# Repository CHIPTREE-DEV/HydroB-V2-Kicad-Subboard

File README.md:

# HydroB-V2-Kicad-Subboard
HydroB-V2-Kicad-Subboard

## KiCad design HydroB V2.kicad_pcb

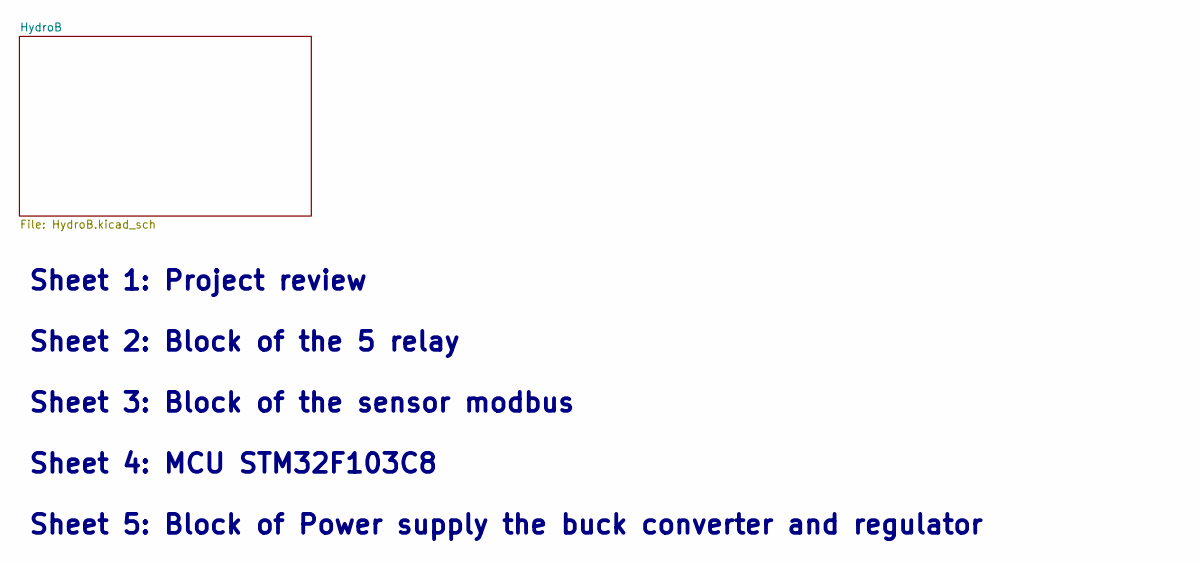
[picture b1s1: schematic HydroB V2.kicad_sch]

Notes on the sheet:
Sheet 1: Project review Sheet 2: Block of the 5 relay Sheet 3: Block of the sensor modbus Sheet 4: MCU STM32F103C8 Sheet 5: Block of Power supply the buck converter and regulator

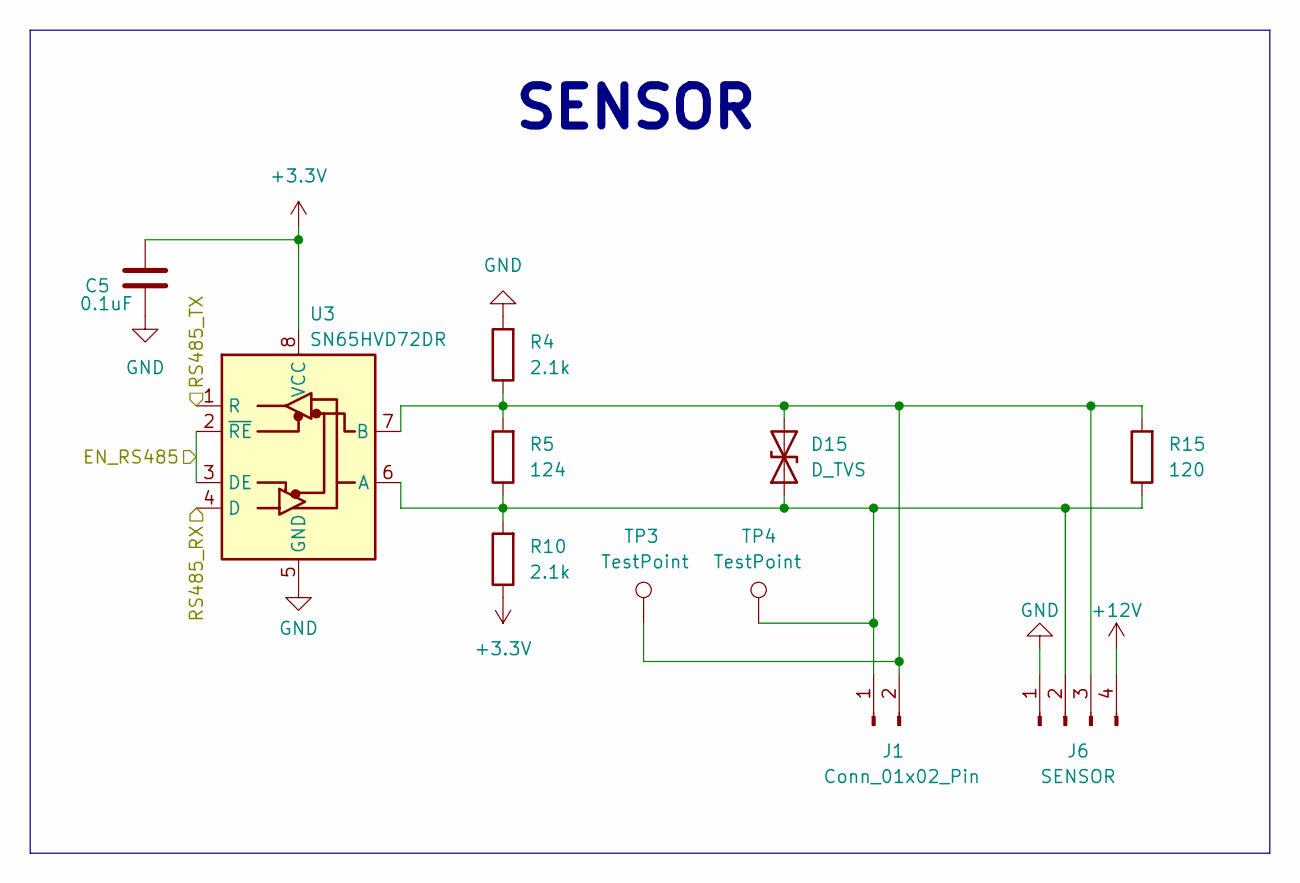
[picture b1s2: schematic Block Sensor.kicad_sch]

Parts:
C5: 0.1uF; C_0603_1608Metric; LCSC C307331
D15: D_TVS; D_SOD-123F
J1: Conn_01x02_Pin; Din sensor
J6: SENSOR; Din sensor 4 Pin
R4, R10: 2.1k; R_0603_1608Metric; LCSC C25744
R5: 124; R_0603_1608Metric; LCSC C25744
R15: 120; R_0603_1608Metric; LCSC C25744
TP3, TP4: TestPoint; TestPoint_Loop_D1.80mm_Drill1.0mm_Beaded
U3: SN65HVD72DR; SOIC-8_3.9x4.9mm_P1.27mm; MFR.Part SN65HVD72DR; LCSC C48125

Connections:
+3.3V: C5.1, R10.1, U3.8 (VCC); also elsewhere on the board
+12V: J6.4; also elsewhere on the board
/HydroB/Block Sensor1/EN_RS485: U3.2 (~RE), U3.3 (DE); also elsewhere on the board
/HydroB/Block Sensor1/RS485_RX: U3.4 (D); also elsewhere on the board
/HydroB/Block Sensor1/RS485_TX: U3.1 (R); also elsewhere on the board
GND: C5.2, J6.1, R4.2, U3.5 (GND); also elsewhere on the board
unnamed: D15.1 (A1), J1.1, J6.2, R5.1, R10.2, R15.1, TP4.1, U3.6 (A)
unnamed: D15.2 (A2), J1.2, J6.3, R4.1, R5.2, R15.2, TP3.1, U3.7 (B)

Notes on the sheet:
SENSOR

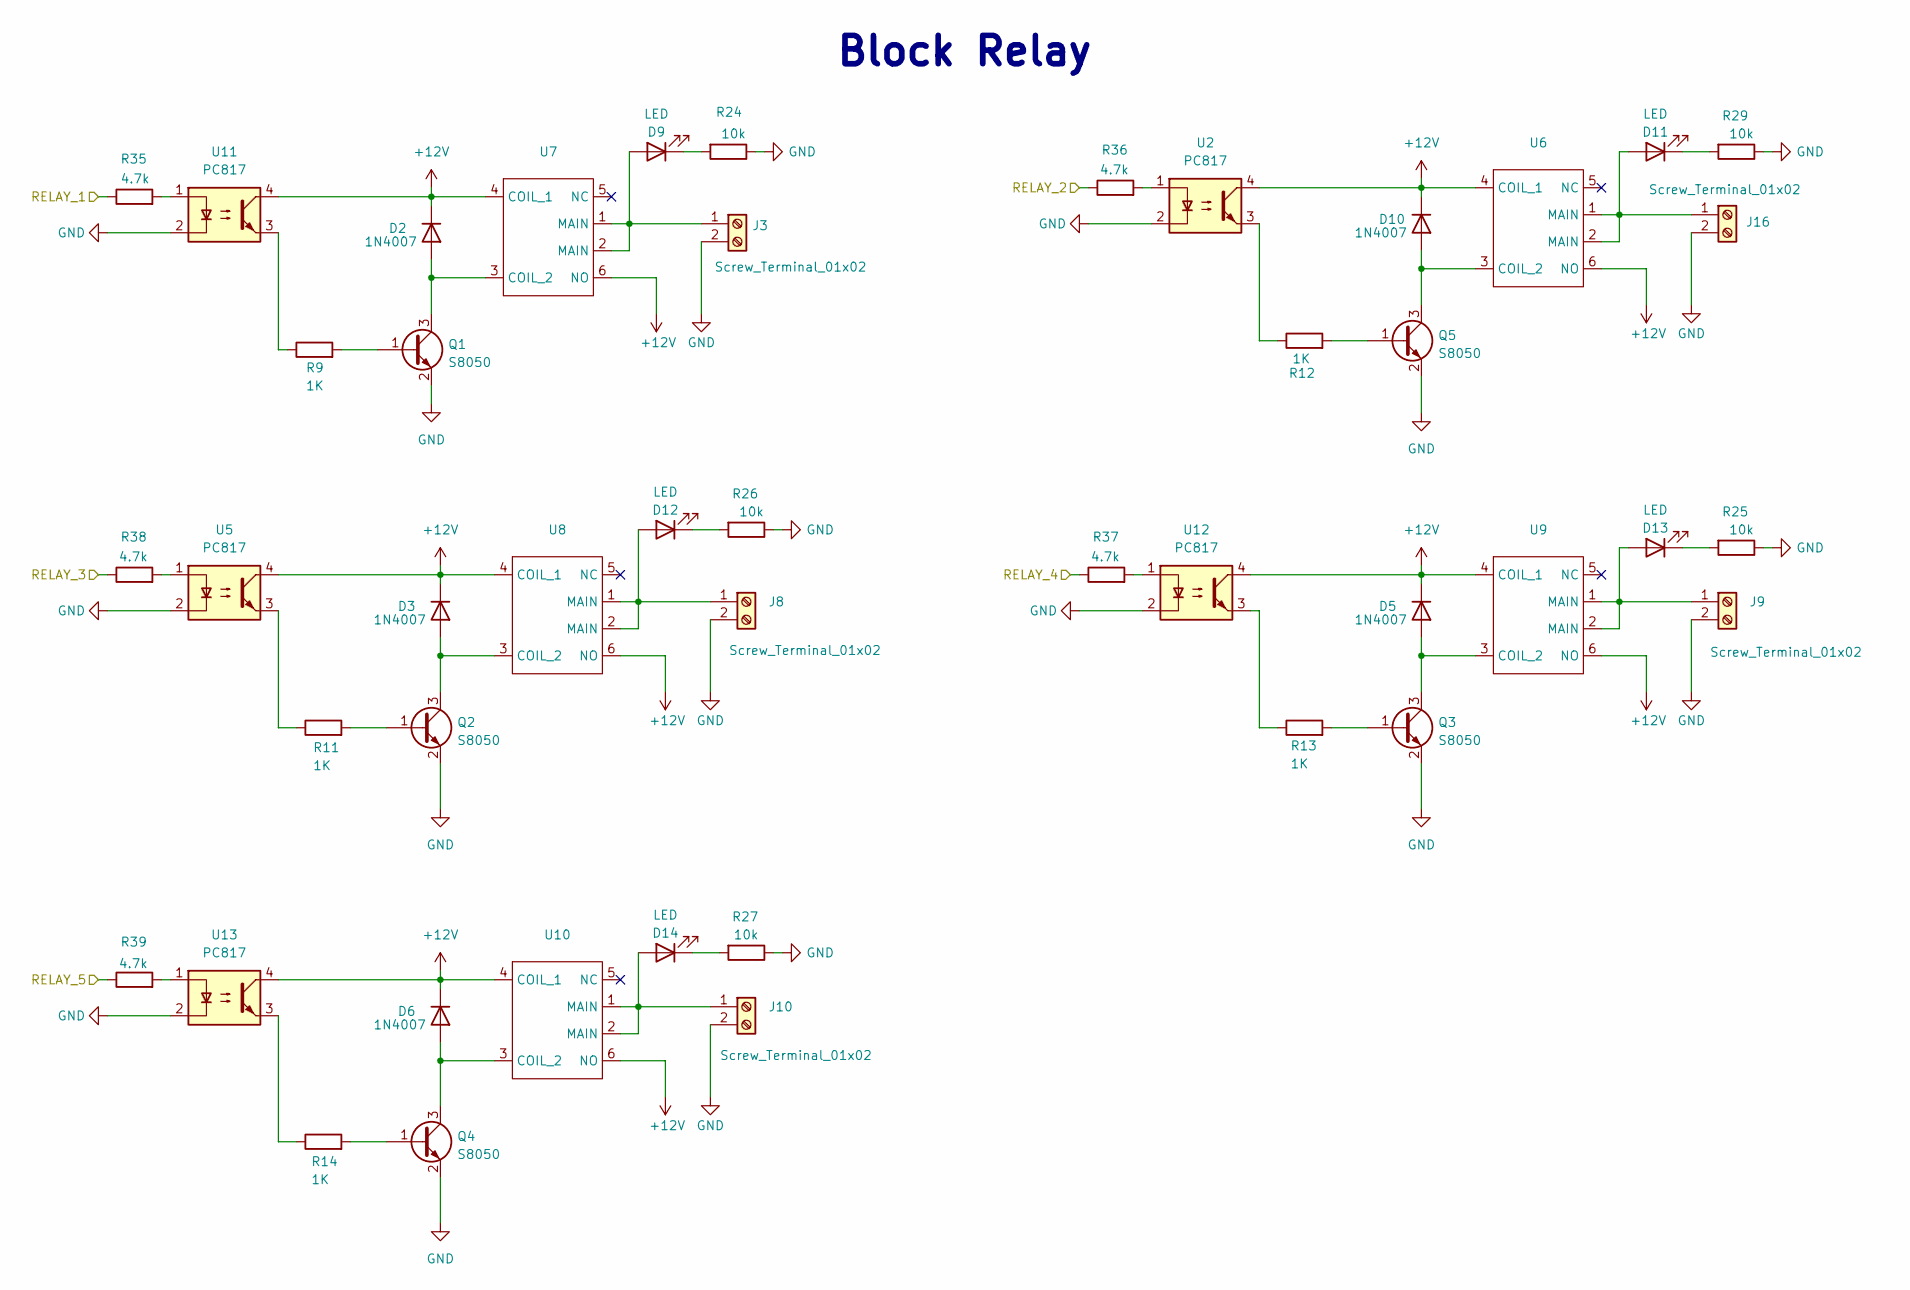
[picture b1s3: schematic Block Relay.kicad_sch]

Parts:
D2, D3, D5, D6, D10: 1N4007; D_SMA
D9, D11, D12, D13, D14: LED; LED_0603_1608Metric
J3, J8, J9, J10, J16: Screw_Terminal_01x02; JST_EH_B2B-EH-A_1x02_P2.50mm_Vertical
Q1, Q2, Q3, Q4, Q5: S8050; SOT-23
R9, R11, R12, R13, R14: 1K; R_0603_1608Metric
R24, R25, R26, R27, R29: 10k; R_0603_1608Metric
R35, R36, R37, R38, R39: 4.7k; R_0603_1608Metric
U2, U5, U11, U12, U13: PC817; DIP-4_W7.62mm_SMDSocket_SmallPads
U6, U7, U8, U9, U10: RELAY-TH_SRS-12VDC-SL

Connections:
+12V: D2.1 (K), D3.1 (K), D5.1 (K), D6.1 (K), D10.1 (K), U2.4, U5.4, U6.4 (COIL_1), U6.6 (NO), U7.4 (COIL_1), U7.6 (NO), U8.4 (COIL_1), U8.6 (NO), U9.4 (COIL_1), U9.6 (NO), U10.4 (COIL_1), U10.6 (NO), U11.4, U12.4, U13.4; also elsewhere on the board
/HydroB/Block Relay1/RELAY_1: R35.1; also elsewhere on the board
/HydroB/Block Relay1/RELAY_2: R36.1; also elsewhere on the board
/HydroB/Block Relay1/RELAY_3: R38.1; also elsewhere on the board
/HydroB/Block Relay1/RELAY_4: R37.1; also elsewhere on the board
/HydroB/Block Relay1/RELAY_5: R39.1; also elsewhere on the board
GND: J3.2, J8.2, J9.2, J10.2, J16.2, Q1.2 (E), Q2.2 (E), Q3.2 (E), Q4.2 (E), Q5.2 (E), R24.1, R25.1, R26.1, R27.1, R29.1, U2.2, U5.2, U11.2, U12.2, U13.2; also elsewhere on the board
unnamed: D2.2 (A), Q1.3 (C), U7.3 (COIL_2)
unnamed: D3.2 (A), Q2.3 (C), U8.3 (COIL_2)
unnamed: D5.2 (A), Q3.3 (C), U9.3 (COIL_2)
unnamed: D6.2 (A), Q4.3 (C), U10.3 (COIL_2)
unnamed: D9.2 (A), J3.1, U7.1 (MAIN), U7.2 (MAIN)
unnamed: D9.1 (K), R24.2
unnamed: D10.2 (A), Q5.3 (C), U6.3 (COIL_2)
unnamed: D11.2 (A), J16.1, U6.1 (MAIN), U6.2 (MAIN)
unnamed: D11.1 (K), R29.2
unnamed: D12.2 (A), J8.1, U8.1 (MAIN), U8.2 (MAIN)
unnamed: D12.1 (K), R26.2
unnamed: D13.2 (A), J9.1, U9.1 (MAIN), U9.2 (MAIN)
unnamed: D13.1 (K), R25.2
unnamed: D14.2 (A), J10.1, U10.1 (MAIN), U10.2 (MAIN)
unnamed: D14.1 (K), R27.2
unnamed: Q1.1 (B), R9.2
unnamed: Q2.1 (B), R11.2
unnamed: Q3.1 (B), R13.2
unnamed: Q4.1 (B), R14.2
unnamed: Q5.1 (B), R12.2
unnamed: R9.1, U11.3
unnamed: R11.1, U5.3
unnamed: R12.1, U2.3
unnamed: R13.1, U12.3
unnamed: R14.1, U13.3
unnamed: R35.2, U11.1
unnamed: R36.2, U2.1
unnamed: R37.2, U12.1
unnamed: R38.2, U5.1
unnamed: R39.2, U13.1

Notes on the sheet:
Block Relay

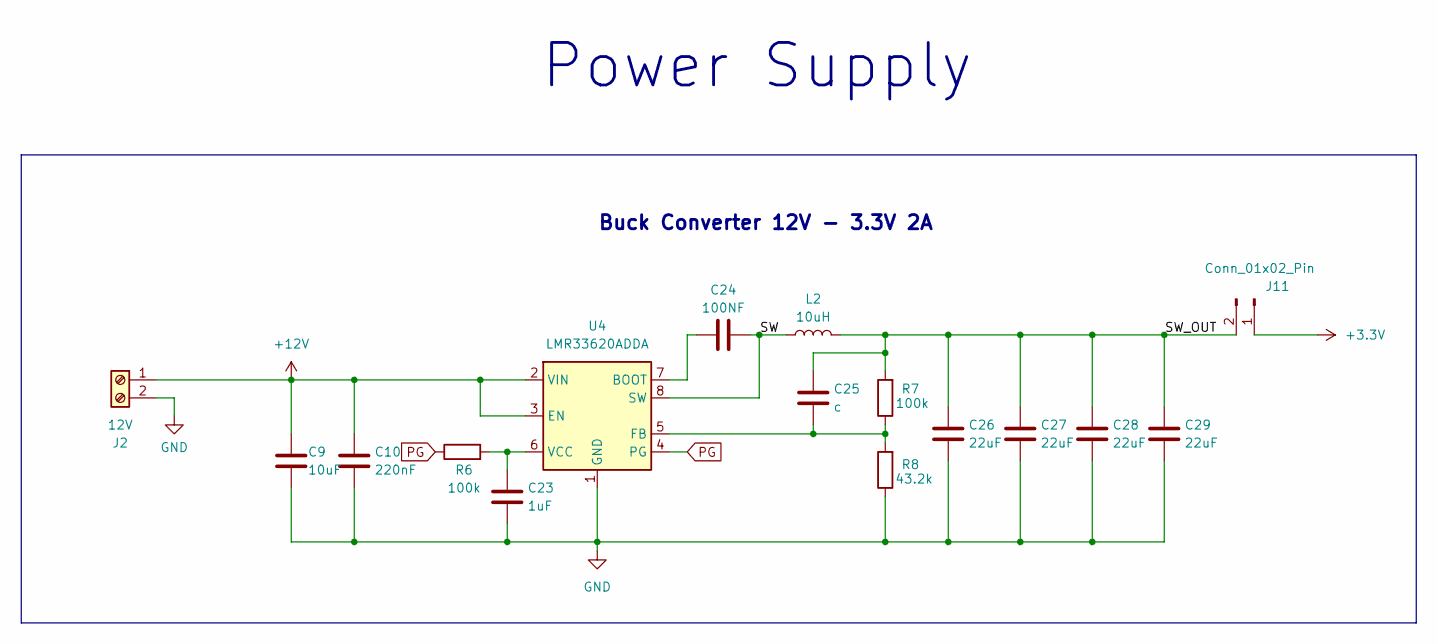
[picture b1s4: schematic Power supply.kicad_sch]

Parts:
C9: 10uF; CP_Elec_4x3
C10: 220nF; C_0805_2012Metric
C23: 1uF; C_0805_2012Metric
C24: 100NF; C_0603_1608Metric
C25: c; C_0805_2012Metric
C26, C27, C28, C29: 22uF; C_0805_2012Metric
J2: 12V; DC conn
J11: Conn_01x02_Pin; PinHeader_1x02_P2.00mm_Vertical
L2: 10uH; L_Bourns_SRP5030T
R6, R7: 100k; R_0603_1608Metric
R8: 43.2k; R_0603_1608Metric
U4: LMR33620ADDA; Texas_HSOP-8-1EP_3.9x4.9mm_P1.27mm_ThermalVias

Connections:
+3.3V: J11.1; also elsewhere on the board
+12V: C9.1, C10.1, J2.1, U4.2 (VIN), U4.3 (EN); also elsewhere on the board
/HydroB/Power Supply1/SW: C24.2, L2.1, U4.8 (SW)
/HydroB/Power Supply1/SW_OUT: C25.1, C26.1, C27.1, C28.1, C29.1, J11.2, L2.2, R7.2
GND: C9.2, C10.2, C23.2, C26.2, C27.2, C28.2, C29.2, J2.2, R8.1, U4.1 (GND), U4.9 (GND); also elsewhere on the board
unnamed: C24.1, U4.7 (BOOT)
unnamed: C25.2, R7.1, R8.2, U4.5 (FB)
unnamed: C23.1, R6.2, U4.6 (VCC)
PG: R6.1, U4.4 (PG)

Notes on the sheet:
Buck Converter 12V - 3.3V 2A
Power Supply

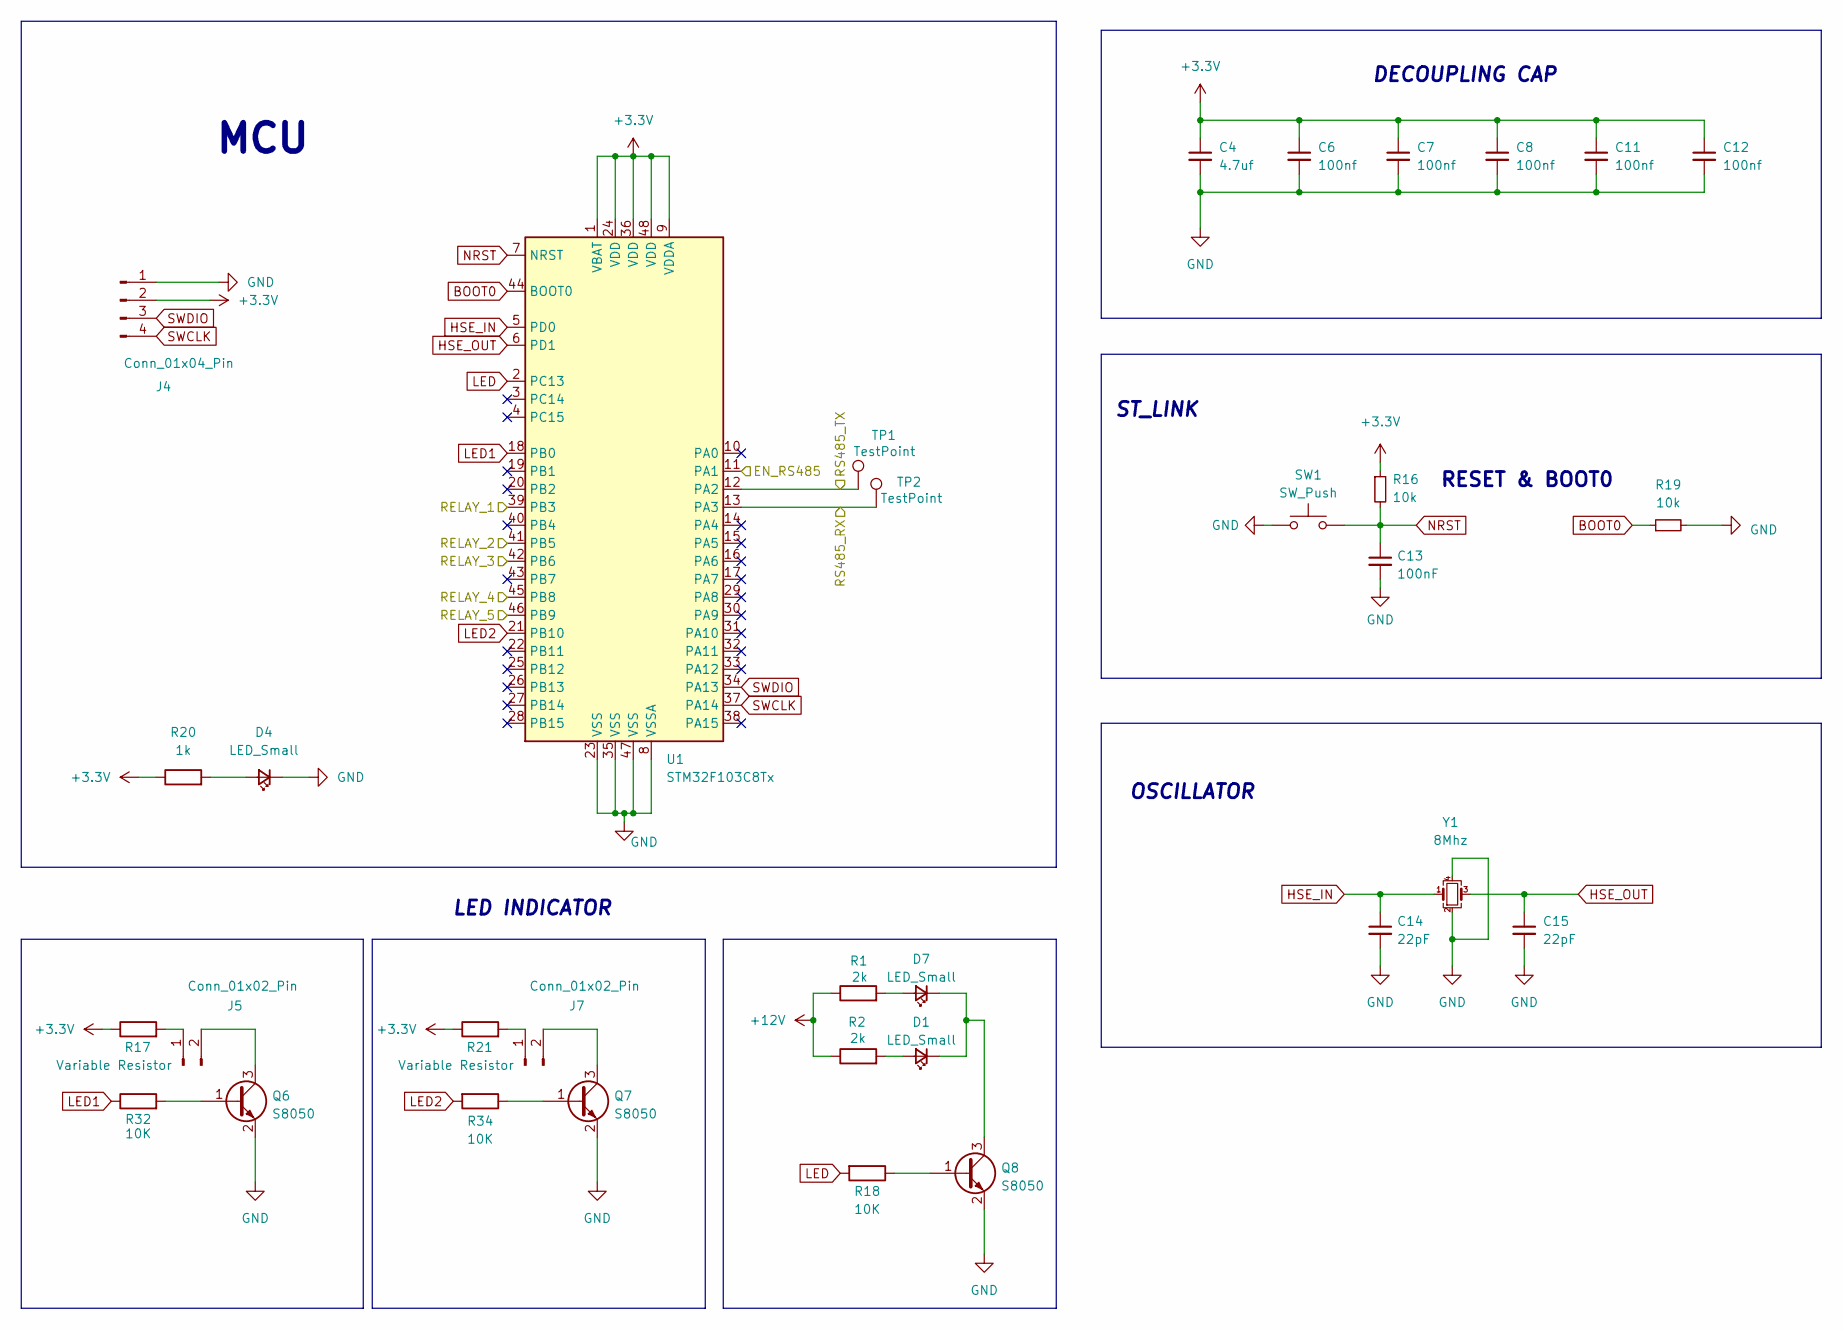
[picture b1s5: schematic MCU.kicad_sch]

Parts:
C4: 4.7uf; C_0805_2012Metric
C6, C7, C8, C11, C12: 100nf; C_0603_1608Metric
C13: 100nF; C_0603_1608Metric
C14, C15: 22pF; C_0603_1608Metric
D1, D4, D7: LED_Small; LED_0805_2012Metric
J4: Conn_01x04_Pin; PinHeader_1x04_P2.00mm_Vertical
J5, J7: Conn_01x02_Pin; JST_EH_B2B-EH-A_1x02_P2.50mm_Vertical
Q6, Q7, Q8: S8050; SOT-23
R1, R2: 2k; R_0603_1608Metric
R16, R19: 10k; R_0603_1608Metric
R17, R21: Variable Resistor; R_0603_1608Metric
R18, R32, R34: 10K; R_0603_1608Metric
R20: 1k; R_0603_1608Metric
SW1: SW_Push; SW_Tactile_SPST_Angled_PTS645Vx39-2LFS
TP1, TP2: TestPoint; TestPoint_Loop_D1.80mm_Drill1.0mm_Beaded
U1: STM32F103C8Tx; LQFP-48_7x7mm_P0.5mm
Y1: 8Mhz; Crystal_SMD_3225-4Pin_3.2x2.5mm

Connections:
+3.3V: C4.1, C6.1, C7.1, C8.1, C11.1, C12.1, J4.2, R16.1, R17.1, R20.1, R21.1, U1.1 (VBAT), U1.9 (VDDA), U1.24 (VDD), U1.36 (VDD), U1.48 (VDD); also elsewhere on the board
+12V: R1.1, R2.1; also elsewhere on the board
/HydroB/Block Relay1/RELAY_1: U1.39 (PB3); also elsewhere on the board
/HydroB/Block Relay1/RELAY_2: U1.41 (PB5); also elsewhere on the board
/HydroB/Block Relay1/RELAY_3: U1.42 (PB6); also elsewhere on the board
/HydroB/Block Relay1/RELAY_4: U1.45 (PB8); also elsewhere on the board
/HydroB/Block Relay1/RELAY_5: U1.46 (PB9); also elsewhere on the board
/HydroB/Block Sensor1/EN_RS485: U1.11 (PA1); also elsewhere on the board
/HydroB/Block Sensor1/RS485_RX: TP1.1, U1.12 (PA2); also elsewhere on the board
/HydroB/Block Sensor1/RS485_TX: TP2.1, U1.13 (PA3); also elsewhere on the board
BOOT0: R19.1, U1.44 (BOOT0)
GND: C4.2, C6.2, C7.2, C8.2, C11.2, C12.2, C13.2, C14.2, C15.2, D4.1 (K), J4.1, Q6.2 (E), Q7.2 (E), Q8.2 (E), R19.2, SW1.1, U1.8 (VSSA), U1.23 (VSS), U1.35 (VSS), U1.47 (VSS), Y1.2, Y1.4; also elsewhere on the board
HSE_IN: C14.1, U1.5 (PD0), Y1.1
HSE_OUT: C15.1, U1.6 (PD1), Y1.3
LED: R18.2, U1.2 (PC13)
LED1: R32.1, U1.18 (PB0)
LED2: R34.2, U1.21 (PB10)
NRST: C13.1, R16.2, SW1.2, U1.7 (NRST)
unnamed: D1.2 (A), R2.2
unnamed: D1.1 (K), D7.1 (K), Q8.3 (C)
unnamed: D4.2 (A), R20.2
unnamed: D7.2 (A), R1.2
unnamed: J5.1, R17.2
unnamed: J5.2, Q6.3 (C)
unnamed: J7.1, R21.2
unnamed: J7.2, Q7.3 (C)
unnamed: Q6.1 (B), R32.2
unnamed: Q7.1 (B), R34.1
unnamed: Q8.1 (B), R18.1
SWCLK: J4.4, U1.37 (PA14)
SWDIO: J4.3, U1.34 (PA13)

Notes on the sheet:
OSCILLATOR
LED INDICATOR
DECOUPLING CAP
ST_LINK
RESET & BOOT0
MCU

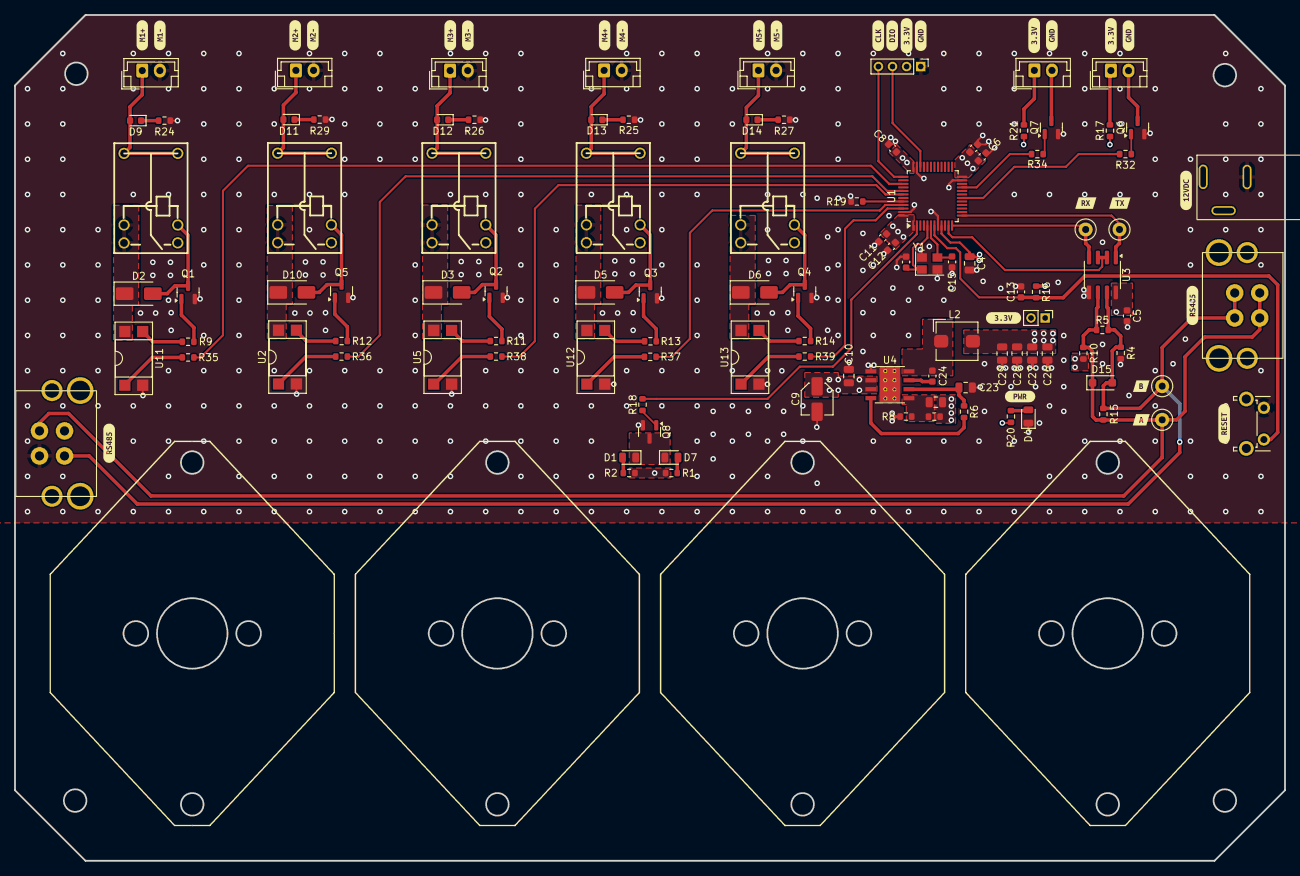
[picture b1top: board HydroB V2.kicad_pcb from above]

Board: 4 copper layers, 180.2 x 120.0 mm, 133 parts (0 on the bottom side), 69 nets.

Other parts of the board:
kibuzzard-66AB4A9F, kibuzzard-66AB4A9F#2, kibuzzard-66AB4A9F#3: G***; kibuzzard-66AB4A9F
kibuzzard-66AB4C8A: G***; kibuzzard-66AB4C8A
kibuzzard-66AB4C8F: G***; kibuzzard-66AB4C8F
kibuzzard-66AB40EF, kibuzzard-66AB40EF#2, kibuzzard-66AB40EF#3: G***; kibuzzard-66AB40EF
kibuzzard-66AC3E8A: G***; kibuzzard-66AC3E8A
kibuzzard-66AC3E80: G***; kibuzzard-66AC3E80
kibuzzard-66AC3EE5, kibuzzard-66AC3EE5#2: G***; kibuzzard-66AC3EE5
kibuzzard-66AC3EFD: G***; kibuzzard-66AC3EFD
kibuzzard-66AC3F5E: G***; kibuzzard-66AC3F5E
kibuzzard-66AC3F67: G***; kibuzzard-66AC3F67
kibuzzard-66AC401E: G***; kibuzzard-66AC401E
kibuzzard-66AC4019: G***; kibuzzard-66AC4019
kibuzzard-66B9A8C9: G***; kibuzzard-66B9A8C9
kibuzzard-66B9A8CF: G***; kibuzzard-66B9A8CF
kibuzzard-66B9A8D4: G***; kibuzzard-66B9A8D4
kibuzzard-66B9A8DE: G***; kibuzzard-66B9A8DE
kibuzzard-66B9A8E4: G***; kibuzzard-66B9A8E4
kibuzzard-66B9A8E9: G***; kibuzzard-66B9A8E9
kibuzzard-66B9A8EF: G***; kibuzzard-66B9A8EF
kibuzzard-66B9A8F6: G***; kibuzzard-66B9A8F6
kibuzzard-66B9A89E: G***; kibuzzard-66B9A89E
kibuzzard-66B9A896: G***; kibuzzard-66B9A896
kibuzzard-66B9A932: G***; kibuzzard-66B9A932

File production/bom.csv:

Designator,Footprint,Quantity,Value,LCSC Part #
C10,0805,1,220nF,
"C11, C12, C13, C24, C6, C7, C8",0603,7,100nf,
"C14, C15",0603,2,22PF,
C23,0805,1,1uF,
C25,0805,1,c,
"C26, C27, C28, C29",0805,4,22uF,
C4,0805,1,4.7uf,
C5,0603,1,0.1uF,C307331
C9,CP_Elec_4x3,1,10uF,
D1,LED_Cree-PLCC4_5x5mm_CW,1,LED_Small,
"D10, D2, D3, D5, D6",D_SMA,5,1N4007,
"D11, D12, D13, D14, D9",0603,5,LED,
D15,D_SOD-123F,1,D_TVS,
"D16, D17, D4, D7, D8",0805,5,LED_Small,
J1,Din sensor,1,Conn_01x02_Pin,
"J10, J16, J3, J8, J9",JST_EH_B2B-EH-A_1x02_P2.50mm_Vertical,5,Screw_Terminal_01x02,
J2,DC conn,1,12V,
J4,PinHeader_1x04_P2.00mm_Vertical,1,Conn_01x04_Pin,
"J5, J7",JST_EH_B2B-EH-A_1x02_P2.50mm_Vertical,2,Conn_01x02_Pin,
J6,Din sensor 4 Pin,1,SENSOR,
L2,L_Bourns_SRP5030T,1,10uH,
"Q1, Q2, Q3, Q4, Q5, Q6, Q7",SOT-23,7,S8050,
"R1, R11, R12, R13, R14, R20, R24, R25, R26, R27, R28, R29, R30, R31, R33, R9",0603,16,1k,
"R10, R4",0603,2,2.1k,C25744
R15,0603,1,120,C25744
"R16, R18, R19, R2, R22, R23, R3, R32, R34",0603,9,10k,
"R17, R21",0603,2,10k,C25744
"R35, R36, R37, R38, R39",0603,5,220R,
R5,0603,1,124,C25744
"R6, R7",0603,2,100k,
R8,0603,1,43.2k,
SW1,SW_Tactile_SPST_Angled_PTS645Vx39-2LFS,1,SW_Push,
U1,LQFP-48_7x7mm_P0.5mm,1,STM32F103C8Tx,
"U10, U6, U7, U8, U9",RELAY-TH_SRS-12VDC-SL,5,~,
"U11, U12, U13, U2, U5",DIP-4_W7.62mm_SMDSocket_SmallPads,5,PC817,
U3,SOIC-8_3.9x4.9mm_P1.27mm,1,SN65HVD72DR, C48125
U4,Texas_HSOP-8-1EP_3.9x4.9mm_P1.27mm_ThermalVias,1,LMR33620ADDA,
Y1,Crystal_SMD_3225-4Pin_3.2x2.5mm,1,8Mhz,

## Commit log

2024-05-20 subboard updated
2024-05-20 finish the subboard layout
2024-06-04 subboard updated for PCB placement
2024-06-14 PCB layout update
2024-06-24 PCB update finalize
2024-06-26 PCB updated
2024-07-11 subboard new update version
2024-07-23 PCB update
2024-07-25 new update
2024-08-01 PCB component placement and layout
2024-08-02 PCB placement
2024-08-08 PCB layout
2024-08-12 Updated project structure and power traces
2024-08-12 Updated label
